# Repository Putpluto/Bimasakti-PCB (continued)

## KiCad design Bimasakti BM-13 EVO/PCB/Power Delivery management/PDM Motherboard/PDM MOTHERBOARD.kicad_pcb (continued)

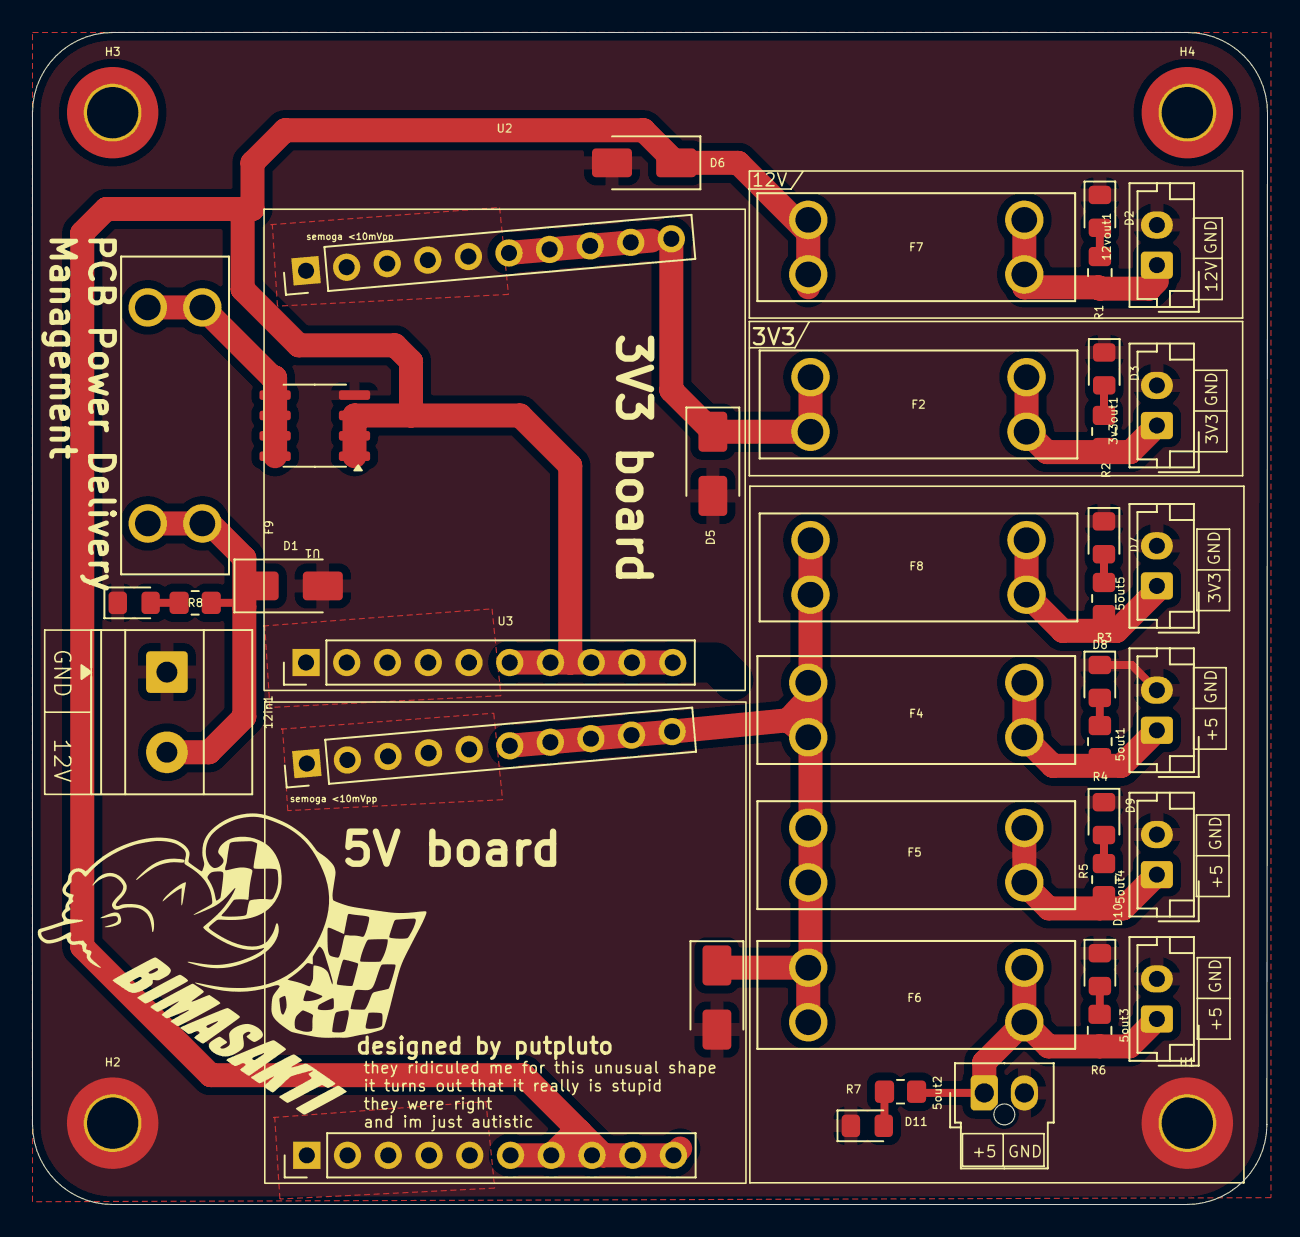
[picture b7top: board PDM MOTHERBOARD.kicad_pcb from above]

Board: 2 copper layers, 77.0 x 73.1 mm, 42 parts (0 on the bottom side), 20 nets.

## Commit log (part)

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2025-04-20 tambah folder telemetry
2025-04-20 tes putra
2025-04-21 Uploaded the programs without additional DATA - Kertya
2025-04-21 diaz belajar coy
2025-04-21 demonstrasi konflik
2025-04-21 pindah folder
2025-04-21 COK NGAREPKU MARAH MARAH
2025-04-21 Revert "COK NGAREPKU MARAH MARAH"
    This reverts commit 9b7e49d627d1466e71e0d3c7c47f17d42c2bbd1f.
2025-04-21 Revert "COK NGAREPKU MARAH MARAH"
    This reverts commit 239a6a5aa163608c927a3338c985238a69e704cd.
2025-04-21 Revert "COK NGAREPKU MARAH MARAH"
    This reverts commit b8804b5bb6f514b2d05ad7de4221242eeb709d1b.
2025-04-21 ini komen denio
2025-04-24 tambah led
2025-04-24 progress motherboard
2025-04-28 Schematic VCU Baru -Kertya
2025-04-28 add footprint library to project
2025-04-28 1111
2025-04-28 test
2025-04-28 test kapasitor
2025-04-28 Revert "1111"
    This reverts commit e328274c36c91817c93686343049b25bcdc91808.
2025-04-28 Revert "1111"
    This reverts commit 5ed0e71407c0feb626f5129f398a39481aa9183a.
2025-04-28 Revert "1111"
    This reverts commit 1bcbada49a9855b0662670e82d97c67a1d40bf7f.
2025-04-28 Revert "add footprint library to project"
    This reverts commit 817adbac281f6a0aec3cf22581ff4d0981cfe032.
2025-04-28 Revert "add footprint library to project"
    This reverts commit c2ea81f1652adadaa2769e08c07f448226fedb71.
2025-04-28 Revert "add footprint library to project"
    This reverts commit 8504fa49bee3609262bd2daef6c4ce7ebcc7244d.
2025-04-28 Baru nambahin CAN Trans
2025-04-28 progress on motherboard pdm
2025-04-29 VCU : Nambah Can, ADS, dan Mosfet -Kertya
2025-04-30 update pdm motherboard
2025-04-30 Arjun Ngirim File Alur VCU
2025-04-30 Aku ngerapiin
2025-04-30 Aku update Telemetry
2025-05-02 update motherboard pdm selesai
2025-05-04 ganti value dan layout
2025-05-04 pdm motherboard sudah 1 size tinggal export stp
2025-05-05 Arjun Ganti
2025-05-05 pdm jadi tapi arjun bakal ngerubah posisi pdm emang anjgg anak satu ini. sama pinnya juga mau dia ganti apalah itu ya allahh capek garap pdm
2025-05-05 ketinggalan hehe
2025-05-05 Arjun Telemetry hari 2
2025-05-05 pdm jadi
2025-05-05 Telemetry
2025-05-06 pdm finishing tambah logo
2025-05-06 torque vectoring
2025-05-07 update TV board
2025-05-07 Arjun Update Finish Telemetry
2025-05-07 Finish Telemetry
2025-05-07 tv board kurang IMU
2025-05-08 Arjun Coba
2025-05-08 Arjunda FInish
2025-05-08 stp to stl
2025-05-10 Arjun Mau Masukin Assembly PCB
2025-05-11 cicil assembly
2025-05-11 Aku Wheelspeed
2025-05-12 PUTRA KONTOL
2025-05-12 Telemetry Finish
2025-05-12 Aku coba
2025-05-13 Aku Telemetry
2025-05-13 Aku VCU
2025-05-13 ngecilin pdm
2025-05-14 pdm selesai ril, tv board sudah bagus kurang cek (mungkin ganti konektor)
2025-05-16 VCU Finish
2025-05-16 buat placeholder baru dan ganti konektor
2025-05-16 Aku Pneumatic
2025-05-16 assembly kurang pneumatic, kurang wiring dudukan motherboard
2025-05-18 assembly VCU FINISH!!!
2025-05-20 detailing
2025-05-21 vcu lebih rapi
2025-05-22 Update submodule reference
2025-05-22 update footprint and pneumatic
2025-05-25 shit i think i fucked up
2025-05-25 wtf was that brooo
2025-05-25 Track large files with Git LFS
2025-05-26 tv dengan pdm kecil
2025-05-26 tes aja
2025-05-27 Remove Git LFS tracking
2025-05-27 lfs kontol
2025-05-27 hapus lfs kontol
2025-05-27 backup
2025-05-27 tele
2025-05-27 del commit
2025-05-30 rapiin
2025-05-30 rapiin file pcb
2025-06-02 vcu fix
2025-06-02 pdm and tv fix
2025-06-03 tv board FIXXXXX
2025-06-03 kontol tadi ga kesave
2025-06-03 tambah i2c di tele
2025-06-03 halo
2025-06-03 SELESAI MOTHERBOARD NEW
2025-06-04 gerber tapi gada drillnya blog
2025-06-04 rapiin sikitlah
2025-06-04 tambah level shifter karena mau dibuat traction control
2025-06-04 awawawaaw jlc
